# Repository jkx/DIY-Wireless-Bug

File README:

DIY Wireless Bug
================

bugOne hardware and software git repos. 

You can find more infos here : 
- Introduction => http://dwb.ilhost.fr/doku.php/start
- Hardware => http://dwb.ilhost.fr/doku.php/bugone:hardware

All works here is under CC Attribution-NonCommercial-ShareAlike licence.
Check out this for licence information :
- http://creativecommons.org/licenses/by-nc-sa/3.0/

Brought to you, by MDL29 Electronic Team 
- http://mdl29.net

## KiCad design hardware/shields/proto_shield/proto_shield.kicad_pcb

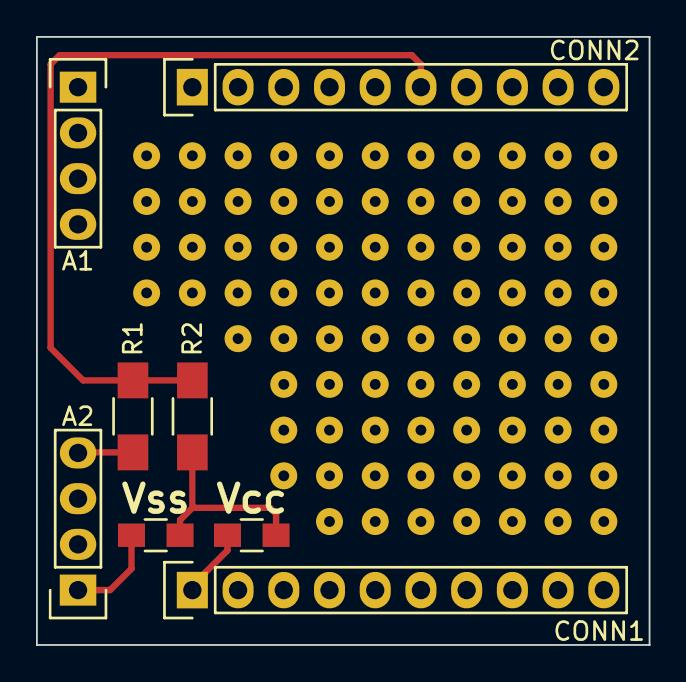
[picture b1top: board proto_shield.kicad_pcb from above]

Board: 2 copper layers, 34.0 x 33.8 mm, 8 parts (0 on the bottom side), 5 nets.

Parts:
A1, A2: CONN_01X04; Pin_Header_Straight_1x04
CONN1, CONN2: CONN_01X10; Pin_Header_Straight_1x10
R1, R2: 470k; R_1206_HandSoldering
R7, R8: 0; R_0805_HandSoldering

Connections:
GND: A1.4, A2.4, CONN1.10, CONN2.10, R1.2
unnamed: R2.1, R7.2, R8.2
PC3: CONN2.6, R1.1, R2.2
VCC: A1.1, A2.2, CONN1.1, R7.1
VSS: A2.1, R8.1

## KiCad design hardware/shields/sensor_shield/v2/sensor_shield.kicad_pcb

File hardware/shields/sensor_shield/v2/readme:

# Board description

This shield is designed to provide different possibilities to create a sensor
shield, for relative humidity, temperature, pressure and lux. All choices do not need to be
soldered. 

The following components can be soldered on the board:
	- Sensirion SHT31D (U1): cheap (~5$ at Farnell) QFP sensor, using I2C for communication
	https://www.sensirion.com/fileadmin/user_upload/customers/sensirion/Dokumente/Humidity_Sensors/Sensirion_Humidity_Sensors_SHT3x_Datasheet_digital.pdf
	- Bosch BME280 (U2) : temperature, humidity and pressure. The package seems more protected than the Sensirion (and we had troubles with the Sensirion which seems to age fast). 
	https://ae-bst.resource.bosch.com/media/_tech/media/datasheets/BST-BME280_DS001-11.pdf
	- Rohm BH1750 (U3) : Light sensor (Luxmeter)
	http://rohmfs.rohm.com/en/products/databook/datasheet/ic/sensor/light/bh1750fvi-e.pdf
	- DS18B20 (U4): popular 1-Wire temperature sensor from Maxim. 
		http://datasheets.maximintegrated.com/en/ds/DS18B20.pdf

C1 stabilizes the power line. Expected value is 100nF.
R1 is the pull-up resistor for 1-Wire bus. Expected value is 4.7kOhm.
R2 and R3 are the pull-up resistors for I2C bus. Values can range from 1.8 to 10k. I prefer using 1.8k (strong pull-up), but the higher the resistance, the lower the current consumption. We use 4.7k on the board
R4 is the pull up resistor for the BH1750 sensor. Along with C2, it provides correct timing for the reset. Ideal values are 1k for R4 and 100n for C1
R5 and R6 are a voltage divider for battery sensing. It divides voltage by 2, allowing a battery up to 6.6V. 
R7 is there to limit current in the ADDR tri state buffer from the BH1750. Expected value is 100k.

U1, U2 and U3 uses I2C.

Shield pinout : 

CONN1_2 : FOUT, PD5
CONN1-5 : 1-Wire bus, PB1
CONN2_4 : SCL, PC5
CONN2_5 : SDA, PC4
CONN2_6 : battery sense, PC3

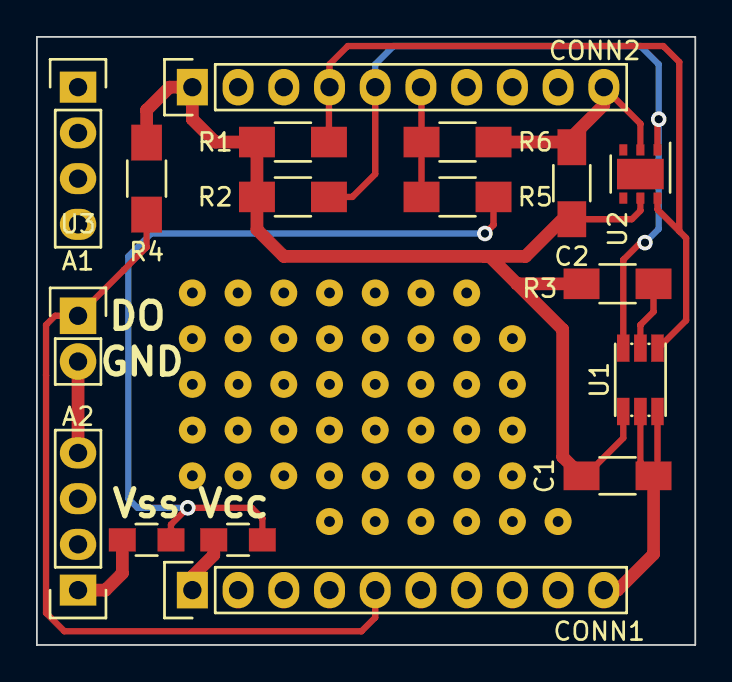
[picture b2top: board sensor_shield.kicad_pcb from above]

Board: 2 copper layers, 36.6 x 33.8 mm, 17 parts (0 on the bottom side), 10 nets.

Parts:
A1, A2: CONN_01X04; Pin_Header_Straight_1x04
C1, C2: 100n; C_1206_HandSoldering
CONN1, CONN2: CONN_01X10; Pin_Header_Straight_1x10
R1, R2: 1.8k; R_1206_HandSoldering
R3: 100k; R_1206_HandSoldering
R4: 4.7k; R_1206_HandSoldering
R5, R6: 200k; R_1206_HandSoldering
R7, R8: 0; R_0805_HandSoldering
U1: TSL2561; TMB6
U2: HTU2XD; DFN-6-1EP_3x3mm_Pitch0.95mm
U3: CONN_01X02; Pin_Header_Straight_1x02

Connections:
GND: A1.4, A2.4, C1.2, C2.2, CONN1.10, CONN2.10, R6.2, U1.2, U1.3, U2.2, U3.2
unnamed: R3.2, U1.5
unnamed: R5.1, R7.2, R8.2
PB1: CONN1.5, R4.2, U3.1
PC3: CONN2.6, R5.2, R6.1
SCL: CONN2.4, R1.2, U1.4, U2.6
SDA: CONN2.5, R2.2, U1.6, U2.1
VCC: A1.1, A2.2, CONN1.1, R8.1
VEE: C1.1, C2.1, CONN2.1, R1.1, R2.1, R3.1, R4.1, U1.1, U2.5
VSS: A2.1, R7.1

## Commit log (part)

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2011-02-20 Added old components
2011-02-20 Added Xmega symbol
2011-02-20 First steps ..
2011-02-20 It will go here ..
2011-02-27 Fixed the AVR-ISP size ..
2011-04-06 not finished yet ...
2011-04-08 Initial PCB test ... + connectors ..
2011-04-25 PCB starting ...
2011-04-26 Added thermal points ...
2011-05-06 Enlarge CONN1 and CONN2
2011-05-22 Almost done ..
2011-05-22 Almost complete ...
2011-05-22 New power supply
2011-05-22 New pcb alim
2011-05-22 Changes on up big connector / power supply .. Ready for review !
2011-05-23 - resize connector holes - moved some silk text
2011-05-23 same ..
2011-06-18 Add labels on connectors
2011-07-27 Initials tests for bugOne.
2011-07-27 Added some infos
2011-09-05 Old stuff cleanup
2011-09-17 Fix compilation script name
2011-09-18 Set clock division to 1
2011-10-11 import aes128 from avr-crypto-lib
2011-10-11 Sample for aes usage
2011-10-11 Add elements in compile script to be able to use aes
2011-10-12 Use timer instead of loop count to send ping
2011-10-12 Clear rx buffer after receive
2011-10-23 Add ping command on sniffer
2011-10-23 Add packet counter
2011-10-23 Specify packet size in send api
2011-11-06 Commit lastest enhancements.
2011-11-07 Initial Makefile migration
2011-11-08 Put core path in a variable
2011-11-20 bugfix .hex + new reset, wrfuses
2011-11-20 Added Makefile
2011-11-22 Add button sample
2011-12-03 Migration to Makefile ..
2011-12-03 Added a skel .. ;)
2011-12-04 Remove source peering, Change values protocol
2011-12-04 Put values manipulations in library
2011-12-04 added error_cmd() and bugfix the run_cmd()
2011-12-04 drop the -V ..
2011-12-04 Add hh10d test ..
2011-12-05 - Disable avrdude check for arduino. - The timer value depends on F_CPU now
2011-12-10 Fix the wrfuses bug
2011-12-10 Fix the fuse bug
2011-12-12 Move functions to the core
2011-12-12 Remove dead code
2011-12-13 Raw sniffer, first version (Hello, Ping, Pong, Values) Test on old version of apps, should work with newest.
2011-12-17 New set.py command to set values. Seems still a bit buggy.
2012-01-05 Use interrupt to increment seconds count
2012-01-22 Fix support for rfm12 lib debug
2012-02-05 Added rfuses
2012-02-10 Added rdfuses
2012-02-11 Removed sniffer.py -> see rfm12.py which contains the real sniffer.
2012-02-12 Ajout projet 18b20 + ethernet
2012-02-12 Add pir project
2012-02-12 Cleanup ..
2012-02-12 Rename Sniffer class according to access method
2012-02-13 Add timeout on uart operation
2012-02-13 Add timeout on the client side
2012-02-13 Fix use of Sniffer python module
2012-02-26 Add testsuite
2012-02-26 Start factoring code from projet to core
2012-02-26 Get devices out of projects
2012-02-26 Use shared devices instead of private one
2012-02-29 Add get tests
2012-03-01 Replace data_t structure with packet_t structure.
2012-03-01 wait for answer of GET query
2012-03-01 Ask the right device
2012-03-11 Change bugone_init signature
2012-03-11 Drop the sniffer code ..
2012-03-11 Drop old hello code
2012-03-11 Drop the build scripts => Makefile rules
2012-03-11 Makefile migration ...
2012-03-11 Removed old blink code.
2012-03-11 Remove old ping project
2012-03-11 Add dht11 project
2012-03-17 Move main() to the framework
2012-03-17 Apply code factorisation to others projects
2012-03-17 import ihm
2012-03-18 New Makefile template (see bugone.inc and lm35/Makefile)
2012-03-18 New sample use of makefile for dht11 project.
2012-03-19 Modified Makefile for sniffer.
2012-03-19 More dynamic graph page
2012-03-19 Add embryonic ihm documentation
2012-03-21 Corrected bugone.inc error.
2012-03-21 Use the right device id..
2012-03-22 Edit devices in node
2012-03-30 Move devices count to init function
2012-03-30 Give the ability for a project to provide his own main()
2012-04-04 Change led init sequence to recognize sniffer board
2012-04-15 Add dht22 device and sample
2012-04-24 Simple RFM12 test project.
2012-04-26 Makefile arrangement
2012-05-07 Added support for optiboot
2012-05-08 new makefile
2012-08-15 Added a fake counter for easy debug ..
2012-08-15 Added a base test "test" app ..
2012-08-15 Added bandgap support ..
2012-08-15 Fix chmod stuff ...
2012-08-15 Fix init led state ..
2012-08-26 Fix compile warning
2012-08-26 Added bootfuses ...
2012-08-27 Deleted old Makefile
2012-08-29 Added FLASH_DATA_FLAG
2012-08-29 Turn On LED1 on boot
2012-09-17 Move django app to sqlite3
2012-09-17 Data are now stored in graphite
2012-09-17 Add sanity check in logger
2012-09-17 Use relative path to import sniffer module
2012-09-17 Remove views
2012-12-04 Change path search for config.h include. Project can now provide their own config structure
2012-12-04 Add current dir in include search path
2012-12-04 Initial import of bugnet ethernet gateway
2013-02-17 Initial import
2013-03-05 - Added support for sleep in rfm12 - Added support for watchdog in bugOne - Went back to bugOne applications
2013-03-05 Added some sleep / blink functions ..
2013-03-10 moved some stuffs ..
2013-03-10 Added the TX_ONLY support case.
2013-03-10 Oops .. fixed the ISR too ..
2013-03-25 You should have installed staticfiles at the previous step
2013-03-25 Smaller logo
2013-04-07 refactoring
2013-07-30 Broke the sleep example .. and decide to do new one in wdt/ dir.
2013-07-30 Fix some merge issue, and switch to bugone_init like boot
2013-07-31 Added comments
2013-07-31 Update to latest das labor rfm12 library
2013-08-01 some tweaks ..
2013-08-25 Missing file (2)
2013-08-25 Added the app .. but still buggy
2013-08-31 Changes : - rename set_apps & get_app to apps_set app_get - added apps_setup(application_t *) - added apps_init()
2013-08-31 Initial guidelines ..
2013-09-01 Only send message every 90 sec ..
2013-09-10 Remove useless project
2013-10-15 power management
2013-12-01 Rename the NO_RFM12 compile flag as it doesn't do what it should. The new name is DISABLE_CORE.
    Added the compile flag : DISABLE_MAIN. It simply don't compile the
    bugone_main.c .. let you write your own main() loop.
2013-12-29 Revert "Merge branch 'master' of github.com:jkx/DIY-Wireless-Bug"
    This reverts commit 687cdaf6833b98e41a089dcf401b3868ba7d4c77, reversing
    changes made to bcd6c78a7226646490949ade666b09978d615e2f.
2014-01-02 Revert "Revert "Merge branch 'master' of github.com:jkx/DIY-Wireless-Bug""
    This reverts commit 52684d4f470facb3a8ea764fa76e93ba7bea94fc.
2014-01-02 Fix the CORE flag
2014-01-26 Add optiboot binarie for those of us without a decent gcc version
2014-01-26 Add optiboot binary for those of us without a decent gcc version
2014-01-26 for jkx
2014-01-26 Updated binaries for optiboot
2014-01-26 Update optiboot binaries
2014-02-04 Support for multiple DNS servers in DHCP reply
2014-02-04 No power managment in bugnet gateway project
2014-03-02 Move watchdog to project
2014-03-03 Fix for the new DISABLE_MAIN flag
2014-03-04 Change for the led
2014-03-07 The default is now PARASITE mode for the DS18B20 because even the external power sensors works in this mode so .. x
2014-07-20 Added test for wakeup on INT
2014-10-24 Minor update on paths in configuration file
2014-10-24 Cleaning up bugOne mini board
    * Added 3 grounded mounting holes (one is near the antenna, usable to
    ground an external antenna)
    * Removed two old capacitors, replaced by one following MCP1700 and
    XC6206 datasheets
    * Set R0 as shunt for regulator, if no regulators are soldered on the
    board.
2014-10-24 Functional mini board
    Added shunt for the MOS and various modification. The only missing element is
    shield connectors label.
2014-10-25 New pilot wire shield for bugOne mini
    This shield allows pilot wire control from bugOne. The shift register needs to
    be checked, but it allows config retention when the AVR is in standby mode with
    minimum energy consumption. The design without the shield register has been
    tested.
    Also added label on bugOne mini board
2014-10-26 Adding pictures of boards for easy online browsing
2014-10-26 Added picture of routed repeater board
    This fixes the previous commit (github does not like amends...)
2014-10-27 Increasing power line on bugOne_mini board
2014-10-28 Rerouted pwr supply part of bugOne mini
    Cleaner routing of power supply, and configuration jumpers added :
    JMP1 to connect V+ (CONN2) to MOS controlled power line or not
    JMP2 to disconnect LDO regulator output from VCC (when using Vcc as an external regulated power line)
2014-10-29 Adding a small power supply board for 1.5V battery operation
    The board is based on a MCP1640 low power regulator. It is compatible as a power header for bugOne mini board.
2014-10-30 Minor modifications on bugOne_mini
2014-10-30 Adding production batches and finalizing labels
2014-10-31 Missing a jumper in bugOne mini
2014-10-31 Increasing clearance between mounting hole and antenna
2014-10-31 Adding missing label on bugOne_mini
2014-11-08 Adding picture of new supply shield
    The shield has been rerouted to correct a mistake. Ground plane was connected to
    all pins, leading to shorts.
    A new feature has also been added to be able to short the MCP1640
2014-11-22 Preliminary support for SHT21 I2C sensor
2014-11-24 Adding "Sleep announce" message
    This message allows proper "node presence" management in the BugNet. Before
    going in sleeping mode, the node sends a message to warn everyone that it will
    not be available. This is especially useful for nodes able to receive commands.
    Commands can be buffered until the node comes back. Receive only device should
    send a "Hello" when waking up
2014-11-30 Cleaning ..
2014-11-30 PNG version ..
2014-12-04 Adding a prototype Teleinfo shield
2014-12-07 Applying coding style
2014-12-10 Fix some typos & remove ds18b20 depends in Makefile
2014-12-13 Adding teleinfo software support
    This is written for the teleinfo shied in the hardware part, based on a simple SFH620A optocoupler for demodulation.
2014-12-14 Back to usbasp programmer
2014-12-26 Changed ds18x20_init to display ROM_CODE and work with both, one or multiple devices
2014-12-26 Astyle is good for this
2014-12-29 Store ds18b20 temperature in a signed int ...
2016-10-03 Adding bugOne helper function for send and receive loop
    The loop prepare data for all application, sends it, and wait for 250 ms for
    received data. It then loops as long as there is data to send and receive.
2016-10-06 Vertical case for bugone
    These have not been tested yet
2016-10-10 Improving apps
    Add types for applications (beta list)
    Add configurability on the duty cycle (all apps does not necessarily need to
    send at each wake up) to save on battery
2016-10-10 Adding a "read" function in bandgap
    This allows bandgap reading in other devices. Bandgap should probably be
    centralized in the core (with ADC?)
2016-10-10 Removing selfish ADC management
2016-10-10 Adding battery in sht21 projects
    Also taking advantage of improvements in duty cycles
2016-10-11 Adding first try at new sensor board
    The board removes useless slots (RJ45, DHT11), and adds new sensors (SHT31D,
    BME280, BH1750). It will also have prototyping zone (2.54mm)
2016-10-12 First placed/routed version
    Need to double check the footprints for BH1750, SHT31D and BME280
2016-10-13 Updated routing
2016-10-13 Fixing alignment on U3
2016-10-13 Adding 1st pin marker on BH1750
2016-10-14 Adding CONFIG packet type
    This packet sends information on the device configuration (for now, only the
    devices and their types)
    It can be use to ease large network management, by sending information on
    available nodes and their devices)
2016-10-19 Adding smaller battery supply
    This one is not pin compatible with the bugOne mini, but it is smaller
    (15mmx20mm) (and with a better layout, according to the MCP1640 datasheet).
2016-10-31 Default to announce sleep
2016-10-31 Blink on recv
2016-10-31 Fixing strange behavior in recv_set
    Return value was not taken into account
2016-11-02 Several global improvements
    - reducing blip time in domonode (was 250ms, is now 25ms, should divide average
    power consumption by 3)
    - making configuration coherent
    - adding a "reply on receive" capability in "set" (changed the app prototype !)
2017-02-20 Fixing empty send
2017-03-07 Adding new KiCad based Sensor V2 shield
2017-03-07 Adding some footprints
2017-03-07 Routing of sensor shield complete
2017-03-07 Minor fixes
2017-03-08 Adding footprint for DS18B20
2017-03-08 Templates can now be used as template on KiCad
